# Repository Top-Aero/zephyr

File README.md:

# Zéphyr

---

## Description

Le vent d'Ouest, fils d'Astreos et d'Éos, attise le feu de notre inspiration : Zéphyr. Projet phare de l'association [Top Aéro](https://www.top-aero.com/), il s'agit d'une fusée expérimentale transsonique dont la coiffe est équipée de capteurs de pression, afin d'observer l'écoulement de l'air qui l'entoure, puis d'en comparer les résultats à une simulation numérique faite préalablement.

Le dépôt Git contient les conceptions des PCB du système électronique et les codes des microcontrôleurs contenus dans la case électronique de la fusée. Ils sont respectivement contenus dans `case_elec` et `code`.

### Structure du dossier `case_elec`

```
case_elec
├───odb
│   └───odb-backups
├───ressources
└───seq
    └───seq-backups
```

Les sous-dossiers odb et seq, désignant respectivement l'ordinateur de bord et le séquenceur embarqués dans la fusée, contiennent des projets KiCAD, le logiciel de CAO pour l'électronique qui a été utilisé durant la phase de conception. Les fichiers de conception, d'extension kicad_pro, kicad_sch et kicad_pcb suffisent à décrire ce qui a été conçu, mais le fichier .gitignore que nous avions rédigé (il sert à filtrer les documents inutiles dans le workflow Git) a été insuffisant. Avec le temps et le ménage qui n'est pas fait, des documents supplémentaires finissent par encombrer les dossiers KiCAD. Il est tout de même intéressant de les décrire :

- les `*.gbr` sont les fichiers de fabrication, générés par le logiciel ;
- les `*.step` sont les fichiers de visualisation 3D de la carte électronique et des composants ;
- les dossiers `*-backups` contiennent les versions précédentes au format zip d'un même projet.

Les -backups se sont avérés vitaux à une ou deux reprises lorsque nous supprimions des éléments critiques par inadvertance. Bien qu'inutiles en soi, ils compensaient le manque de maîtrise que l'on avait de Git et de KiCAD et faisaient gagner beaucoup de temps. À l'avenir, il faudra penser à configurer KiCAD pour ne conserver que la dernière version, car c'est la plus utile en cas de pépin.

#### Structure du dossier `ressources`

```
ressources
├───3Dmodels
│   └───teensy
├───lib_fp
│   ├───Adafruit BNO055
│   │   ├───Adafruit BNO055-backups
│   │   └───Adafruit BNO055.pretty
│   ├───Adafruit Ultimate GPS
│   │   └───Adafruit Ultimate GPS-backups
│   ├───Adafruit_sensors.pretty
│   ├───Adafruit_Ultimate_GPS
│   │   ├───Adafruit_Ultimate_GPS-backups
│   │   └───Adafruit_Ultimate_GPS.pretty
│   ├───common_misc.pretty
│   ├───MPL3115A2_v0.2
│   │   ├───MPL3115A2_v0.2-backups
│   │   └───MPL3115A2_v0.2.pretty
│   ├───Reyax.pretty
│   └───teensy.pretty
├───lib_sch
└───tmp_resources
    ├───Adafruit-BNO055-Breakout-PCB-master
    │   └───assets
    ├───Adafruit-MPL3115A2-PCB-master
    │   └───assets
    ├───prj
    │   └───altimetre
    └───zip
```

Le dossier ressources se structure ainsi :

- 3Dmodels : contient les modèles 3D des composants. Utile pour la visualisation et l'export au format .step ;
- lib_fp : *library footprints*, contient les empreintes des composants utilisés, c'est-à-dire leur contour et les trous à placer sur la carte électronique ;
- lib_sch : *library schematics*, contient les symboles électriques utilisés dans les schémas électriques ;
- liensUtiles.txt : contient des liens vers des bibliothèques d'empreintes, de symboles électriques et de modèles 3D.
- tmp_ressources : un dossier un peu fouillis qu'il faudrait prendre le temps de réhabiliter.

Le fichier liensUtiles.txt porte mal son nom, car les sites vers lesquels il renvoie se sont avéré moins utiles qu'espérés : des composants complexes comme les capteurs Adafruit n'y sont pas documentés. Il a fallu, et il a mieux valu concevoir par nous même les empreintes, même approximativement. Par ailleurs, Adafruit met à disposition des modèles 3D de leurs composants sur [cette page GitHub](https://github.com/adafruit/Adafruit_CAD_Parts). Toutes les entreprises n'en font pas autant.

### Structure du dossier `code`

```
code
├───seq
├───station-sol
└───telemetrie
    ├───TopAeroEM
    ├───TopAeroEM0720
    ├───TopAeroEM_test_pitot
    └───TopAeroRV
```

Les dossiers seq, TopAEroEM (EM pour émission) et TopAéroRV (RV pour récéption...) dans telemetrie contiennent des fichiers ino. C'est le format de fichier que reconnaît l'éditeur Arduino que l'on utilisait pour programmer les microcontrôleurs de la case électronique. Pour plusieurs raisons, il faut lui préférer à l'avenir son alternative PlatfomIO soit en tant qu'extension, soit en standalone à intégrer au workflow de votre IDE de choix. Pour les experts, un makefile Arduino peut suffire.

Plusieurs dossiers TopAeroEM se côtoient. Une convention de nommage récurrente est de suffixer à une autre version d'un même dossier le mois puis le jour où cette version a vu le jour, en quatre chiffres. Ainsi, le dossier TopAeroEM0720 est une version de TopAeroEM créée un 20 juillet. Des exceptions subsistent (TopAeroEM_test_pitot), mais tant qu'elles ne sont pas nombreuses (plus que 2), elles restent gérables. Ces deux pratiques sont tout de même à éviter, car elles ne tirent pas profit de la technologie de versionnage de Git. Il faut préférer mettre à jour le code existant, ou encore ajouter une nouvelle branche au projet, ou dans le pire des cas, se passer complètement du workflow Git si le contraire amenait à désorganiser la structure du projet.

Le dossier station-sol contient plusieurs scripts qui n'ont pas pu être déployés. Le seul script utilisable en l'état est simpleUSBlogger.py qui se charge d'écrire dans un fichier les données réceptionnées.

## Derniers mots

La fusée a décollé un jour de juillet 2022. À part quelque modifications mineures et sporadiques sur sa page GitHub, le projet est terminé.

## Contacts

Nom               | Rôle                              | Contact
------------------|-----------------------------------|----------
Mohamed-Iadh Bani | Conception séquenceur             | [:e-mail:](mailto:mohamed-iadh.bani@top-aero.com) [:octocat:](https://github.com/mediadhBani)
Théo Tugayé       | Conception ordinateur de bord     | [:e-mail:](mailto:theo.tugaye@top-aero.com) [:octocat:](https://github.com/Alhucarr)

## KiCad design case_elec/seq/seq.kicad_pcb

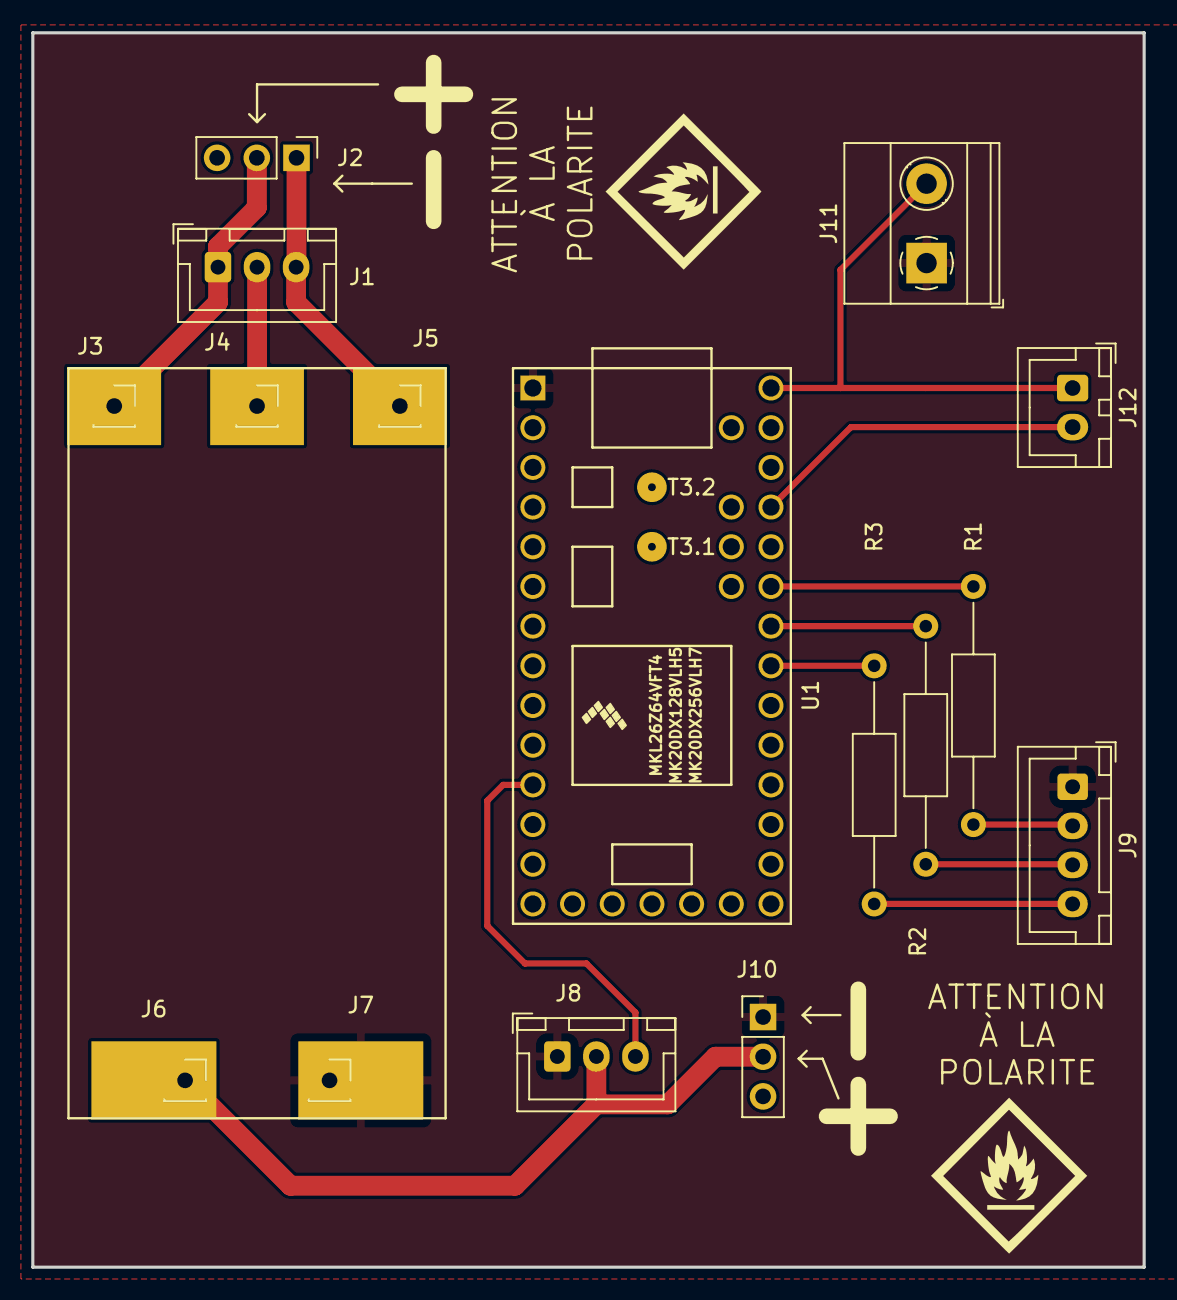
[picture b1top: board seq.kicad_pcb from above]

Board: 2 copper layers, 71.1 x 79.0 mm, 16 parts (0 on the bottom side), 14 nets.

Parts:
J1: LiPo BMS; JST_XH_B3B-XH-A_1x03_P2.50mm_Vertical
J2: Lipo Alim; PinHeader_1x03_P2.54mm_Vertical
J3: B+; PinSocket_1x01_P2.54mm_Vertical
J4: BM; PinSocket_1x01_P2.54mm_Vertical
J5: B-; PinSocket_1x01_P2.54mm_Vertical
J6: P+; PinSocket_1x01_P2.54mm_Vertical
J7: P-; PinSocket_1x01_P2.54mm_Vertical
J8: Servo; JST_XH_B3B-XH-A_1x03_P2.50mm_Vertical
J9: LEDs; JST_XH_B4B-XH-A_1x04_P2.50mm_Vertical
J10: Alim secours; PinHeader_1x03_P2.54mm_Vertical
J11: Coupleur; TerminalBlock_Phoenix_MKDS-1,5-2-5.08_1x02_P5.08mm_Horizont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
J12: Jack; JST_XH_B2B-XH-A_1x02_P2.50mm_Vertical
R1, R2, R3: R100; R_Axial_DIN0207_L6.3mm_D2.5mm_P15.24mm_Horizontal
U1: Teensy3.2; Teensy30_31_32_LC

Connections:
/B+: J1.1, J2.2, J3.1
/B-: J1.3, J2.1, J5.1
/BM: J1.2, J4.1
GND: J7.1, J8.1, J9.1, J10.1, J11.1, U1.1 (GND)
unnamed: J8.3, U1.11 (9_RX2_CS_PWM)
unnamed: J9.2, R1.1
unnamed: J9.3, R2.1
unnamed: J9.4, R3.1
unnamed: J6.1, J8.2, J10.2
unnamed: J12.2, U1.30 (23_A9_Touch_PWM)
unnamed: R1.2, U1.28 (21_A7_RX1_CS_PWM)
unnamed: R2.2, U1.27 (20_A6_CS_PWM)
unnamed: R3.2, U1.26 (19_A5_SCL0_Touch)
VCC: J11.2, J12.1, U1.33 (Vin)

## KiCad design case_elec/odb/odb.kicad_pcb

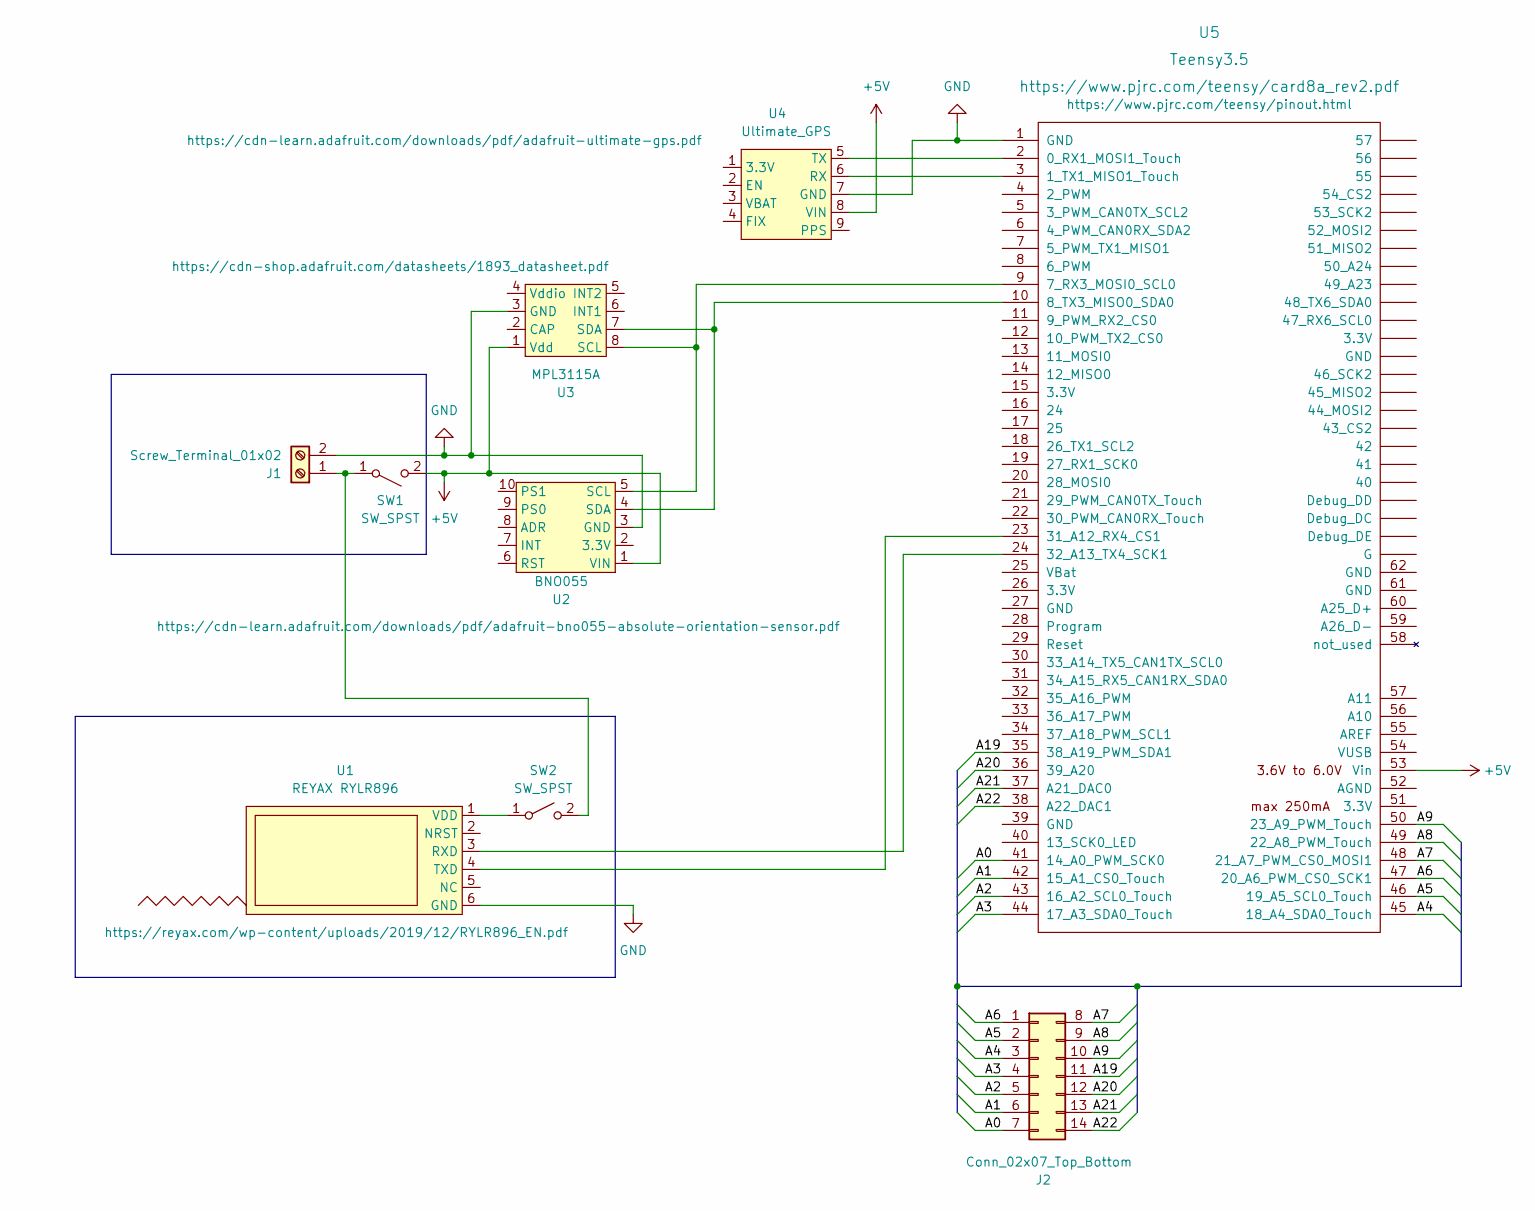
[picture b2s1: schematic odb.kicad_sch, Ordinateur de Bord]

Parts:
J1: Screw_Terminal_01x02; TerminalBlock_Phoenix_MKDS-1,5-2-5.08_1x02_P5.08mm_Horizont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
J2: Conn_02x07_Top_Bottom; Molex_Nano-Fit_105310-xx14_2x07_P2.50mm_Vertical
SW1, SW2: SW_SPST; SW
U1: REYAX RYLR896; RYLR896
U2: BNO055
U3: MPL3115A; MPL3115A2
U4: Ultimate_GPS
U5: Teensy3.5; Teensy35_36

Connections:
+5V: SW1.2 (B), U2.1 (VIN), U3.1 (Vdd), U4.8 (VIN), U5.53 (Vin)
/A0: J2.7, U5.41 (14_A0_PWM_SCK0)
/A1: J2.6, U5.42 (15_A1_CS0_Touch)
/A2: J2.5, U5.43 (16_A2_SCL0_Touch)
/A3: J2.4, U5.44 (17_A3_SDA0_Touch)
/A4: J2.3, U5.45 (18_A4_SDA0_Touch)
/A5: J2.2, U5.46 (19_A5_SCL0_Touch)
/A6: J2.1, U5.47 (20_A6_PWM_CS0_SCK1)
/A7: J2.8, U5.48 (21_A7_PWM_CS0_MOSI1)
/A8: J2.9, U5.49 (22_A8_PWM_Touch)
/A9: J2.10, U5.50 (23_A9_PWM_Touch)
/A19: J2.11, U5.35 (38_A19_PWM_SDA1)
/A20: J2.12, U5.36 (39_A20)
/A21: J2.13, U5.37 (A21_DAC0)
/A22: J2.14, U5.38 (A22_DAC1)
GND: J1.2, U1.6 (GND), U2.3 (GND), U3.3 (GND), U4.7 (GND), U5.1 (GND)
unnamed: J1.1, SW1.1 (A), SW2.2 (B)
unnamed: SW2.1 (A), U1.1 (VDD)
unnamed: U1.3 (RXD), U5.24 (32_A13_TX4_SCK1)
unnamed: U1.4 (TXD), U5.23 (31_A12_RX4_CS1)
unnamed: U2.4 (SDA), U3.7 (SDA), U5.10 (8_TX3_MISO0_SDA0)
unnamed: U2.5 (SCL), U3.8 (SCL), U5.9 (7_RX3_MOSI0_SCL0)
unnamed: U4.5 (TX), U5.2 (0_RX1_MOSI1_Touch)
unnamed: U4.6 (RX), U5.3 (1_TX1_MISO1_Touch)

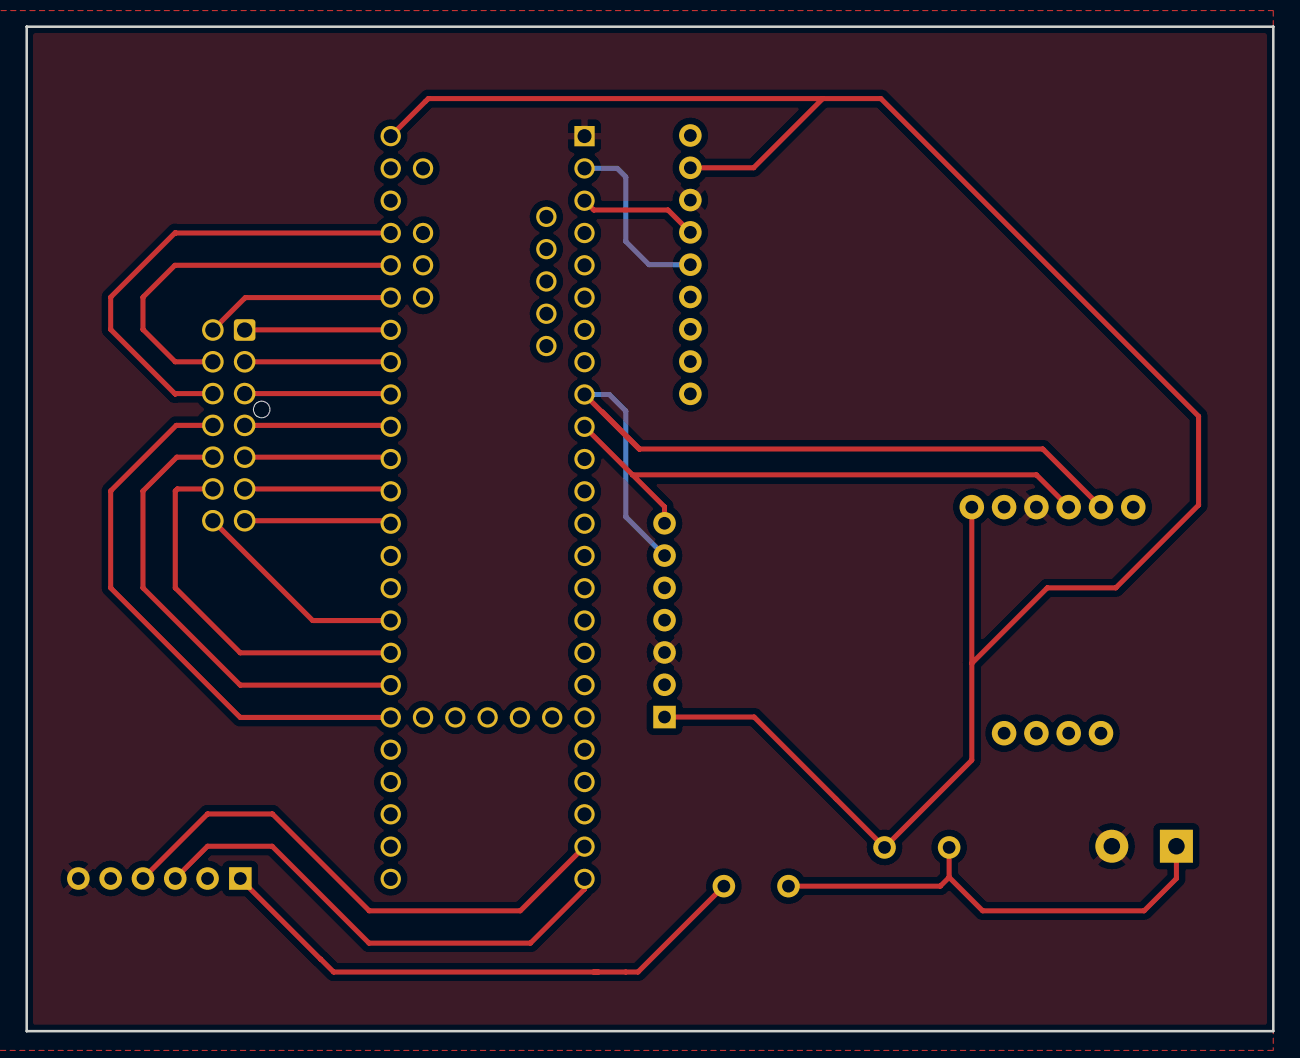
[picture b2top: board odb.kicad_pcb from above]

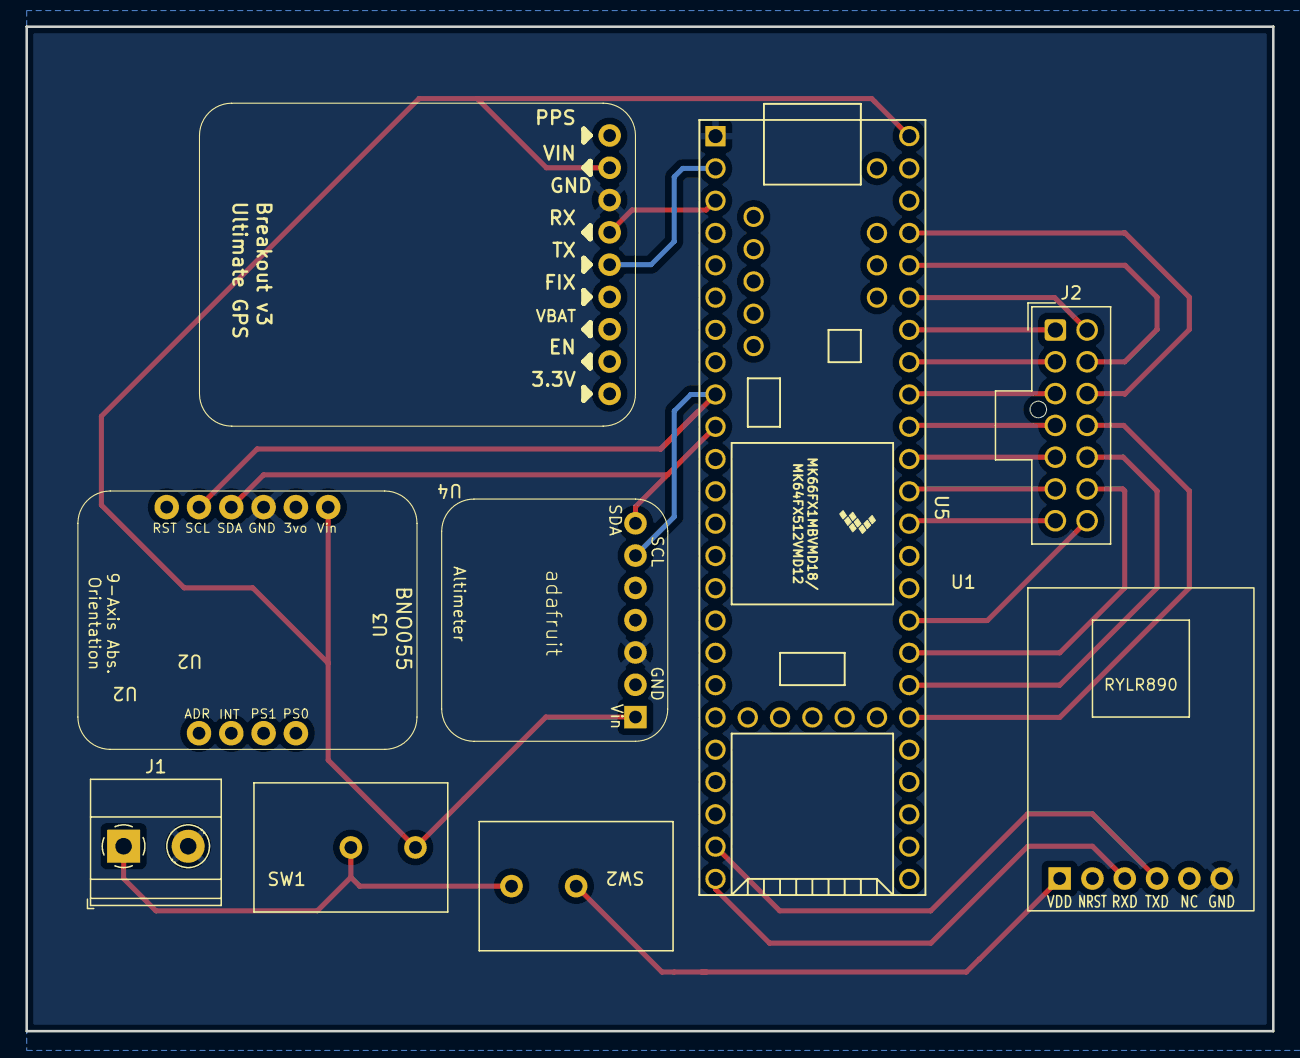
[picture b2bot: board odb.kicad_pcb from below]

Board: 2 copper layers, 98.0 x 79.0 mm, 9 parts (9 on the bottom side), 24 nets.

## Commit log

2022-05-27 ajout dossiers de travail
2022-05-28 Ajout des capteurs
2022-05-28 Connexion SDA/SCL
2022-05-28 ajout schematic module lora
2022-05-28 Ajout des footprint
2022-05-28 Ajout des footprint dans la bibliotheque
2022-05-28 modifications mineures
2022-05-28 Ajouts de composants et connexions
    - molex
    - interrupteurs x2
    - module lora
2022-05-28 complétion du schéma électrique
2022-05-29 Mise à jour du pcb
2022-05-29 ajout des librairies teensy
    N.B. : chacun devra l'ajouter dans son gestionnaire de librairie, global de préférence
2022-05-30 agencement approximatif des composants du pcb
2022-05-31 remplacement des bords Edge.Cuts par F.Silkscreen
2022-05-31 intervertion des labels de pins 4 et 5
2022-05-31 pcb en cours de tracé
2022-06-01 Ajout du plan de masse + intercom
2022-06-01 Jade's participation
2022-06-01 inversion de pins
2022-06-01 correction de pin répété
2022-06-01 complétion du pcb
2022-06-01 ajout de zones keepout
2022-06-01 modifications globales et fichiers gerber INACHEVES
2022-06-01 gerbers mis à jour
2022-06-11 code servo commandable par potentiomètre
2022-06-11 code test pour stepper
2022-06-11 ajouts divers
2022-06-14 Ajout du code de réception
2022-06-14 ajout d'un flag de debug
2022-06-14 Correction d'espacement + nettoyage du file system du projet
2022-06-14 Oupsi
2022-06-14 réorganisation des lib
2022-06-15 ajout symbole BMS
2022-06-16 amélioration route sw
2022-06-16 ajout pcb séquenceur
2022-06-17 Nouveau mapping perçage + gerber
2022-06-18 sauvetage, màj seq version à usiner
2022-06-23 màj et génération des fichiers de fabrication
    les silkscreens et masks ont été ajoutés pour les les deux côtés du pcb, au cas où
2022-06-24 Lisezmoi.md
    Ils sont beaux nos badges ?
2022-06-24 Ajout du lien du site de top aéro
2022-06-25 Pins alternatifs + suppressions des warnings
2022-06-25 Ajout d'une piste SCL pour l'alitmètre en panique
2022-06-25 Suppression du pin
2022-06-25 Migration code sequenceur vers PlatformIO
    Note : il manque le dossier de configuration .pio (et .vscode si créé via VSCode) dans le dossier de code du sequenceur. Recréer le projet PlatformIO qui reprend le dossier pour le rendre compilable 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
2022-06-26 Suppression de la deuxième smd + modification sur le schema
2022-06-26 Ajout de pistes B.Cu
    Alternative à :
    - resistances 0 Ohm
    - modification du pinout de la Teensy 3.5
    Attention : les gerbers n'ont pas été générés.
2022-06-26 Amélioration tracé pistes
2022-06-26 Ajout du plan de masse sur l'autre layer
2022-06-26 transi platformIO
2022-07-02 Ajout du code de l'odb en version PlatformIO
2022-07-02 ajout de readme et debut de code pour sequenceur
2022-07-05 réaménagement global
2022-07-06 Remise en marche du code séquenceur de l'an dernier
2022-07-07 Amélioration du code + fsm multitache
2022-07-13 Barometer library use + old code commented
2022-07-14 nettoyage du code
2022-07-14 Suppression des commentaires, lissage du code et de l'affichage
2022-07-15 màj mineure
2022-07-17 Mise ànjour des capteurs analog
2022-07-18 Retour du code altimetre optimisé + ajout de délais de loop
2022-07-19 corrections éparses
2022-07-19 lutte sans merci contre le servomoteur
2022-07-21 solution partielle pio de secours incomplète et non correspondantes à la version finale
    aucun intérêt si ce n'est de conserver l'historique des modifications
2022-08-14 solution finale utilisée en vol
2022-08-14 Révision du readme
2022-11-07 Ajout de documentation de fin de développement
    - édition du readme
    - réorganisations mineures de fichiers
2022-11-16 Corrections mineures
2022-11-16 encore des erreurs d'orthographes corrigées
